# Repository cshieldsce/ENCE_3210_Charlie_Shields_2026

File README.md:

# ENCE 3210 - Microprocessor Systems I
All my labs, projects, and drivers for Microprocessor Systems I, Winter 2026.

---

## Project Documentation

### Documentation B - DAC Prototype & KiCad
> 📁 [`Documentation_B/`](Documentation_B/README.md)

- 5-bit R-2R DAQ prototype built in lab and verified on oscilloscope
- Falstad circuit simulation
- KiCad schematic and PCB layout files for the Arduino UNO Shield

### Documentation C - DSP Shield
> 📁 [`Documentation_C/`](Documentation_C/README.md)

Full documentation for the DSP Shield design and fabrication.

- Shield specifications and block diagram
- 10-bit R-2R Ladder DAC design and prototype
- KiCad PCB schematic, layout, 3D renders, and gerber files
- Interactive BOM
- Live demo videos of firmware running on the shield

---

## Labs

### Lab 1 — More C Practice
> 📁 [`lab1_embedded_c/`](labs/lab1_embedded_c/README.md)

Exercises practicing fundamental C programming concepts on embedded targets.

- Calculate twice the square of integers 0–511
- Cosine calculation for degrees 0–360 (results stored in array)
- Find the second maximum value in a 50-element integer array

---

### Lab 2 — Interrupts
> 📁 [`lab2_interrupts/`](labs/lab2_interrupts/README.md)

C programs using Interrupt Service Routines (ISRs) on the Arduino UNO.

- **Button Counter:** Count presses of two buttons via ISR; drive RGB LED based on difference
- **LED Sequence Control:** Cycle through R → RG → RGB → GB → B → RB on button press
- **Simple Calculator:** ISR-driven arithmetic operations
- **Filtering Operation:** Basic signal filtering using interrupts

---

### Lab 3 — Asynchronous Tasks with Interrupt Timers
> 📁 [`lab3_async_tasks/`](labs/lab3_async_tasks/README.md)

Two background tasks and one foreground task running concurrently using hardware timers.

| Task | Frequency | Timer | Responsibility |
|---|---|---|---|
| Task 1 | 1 Hz | Timer 1 | Blink Green LED, increment main-task counter |
| Task 2 | 10 Hz | Timer 2 | Additional async operation |
| Main | — | — | Foreground logic driven by Task 1 counter |

Also includes a **5-bit R-2R DAQ circuit** built and tested with oscilloscope verification.

---

### Lab 4 — Firmware Engineering
> 📁 [`lab4_firmware/`](labs/lab4_firmware/README.md)

Firmware design exercises built and tested on the DSP Shield.

- **Exercise 2 — Solar Charger:** Firmware for a solar charging control system
- **Exercise 4 — Fan Controller:** PWM-based fan speed controller with block diagram

> Demo videos for both projects available in [`Documentation_C/`](Documentation_C/README.md#shield-demos)

---

## HAL Drivers
> 📁 [`HAL_Drivers/`](HAL_Drivers/README.md)

Reusable hardware abstraction layer drivers developed during the course.

| Driver | Description |
|---|---|
| `ADCs_Uno/` | ADC read utilities for Arduino UNO |
| `PWMs_Uno/` | PWM output utilities for Arduino UNO |
| `HC_SR04_Drivers_v1/` | HC-SR04 ultrasonic sensor driver (v1) |
| `HC_SR04_Drivers_v2/` | HC-SR04 driver with interrupt support (v2) |
| `HC_SR04_Drivers_v3/` | HC-SR04 driver with filtered output (v3) |
| `MPU6050_Test/` | MPU-6050 IMU (I2C) test and driver |
| `SSD1306_Test/` | SSD1306 OLED HAL driver test |

---

## C Workshop
> 📁 [`c_workshop/`](c_workshop/README.md)

Warm-up C programming exercises completed at the start of the course.

- `quadratic.c` — Solve quadratic equations using a struct to return both roots
- `scanf_for_loop.c` — User input processing with for loops

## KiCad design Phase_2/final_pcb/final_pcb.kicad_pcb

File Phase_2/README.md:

# Phase 2 - DemoSat PCB Design

**ENCE 3210 Microprocessors 1 | Winter Quarter 2026 | Final Project**
**Created by: Charlie Shields**

---

## Overview

This phase contains the final custom PCB design for the DemoSat project — a sensor data logging system built around an Arduino Uno (ATmega328P). The board interfaces with multiple sensors, logs data to a microSD card, and provides visual status indicators.

---

## System Block Diagram

---

## PCB Preview

### Front Silkscreen

### 3D Render

---

## System Architecture

The PCB acts as a shield/carrier board for the Arduino Uno and integrates the following components:

| Component | Function | Interface |
|---|---|---|
| SparkFun LIS3DH Breakout | 3-Axis Accelerometer | I2C (SDA/SCL) |
| Adafruit MS8607 | External Temp, Humidity, Pressure | I2C (SDA/SCL) |
| TMP36 | Internal Temperature Sensor | Analog (A0) |
| SparkFun OpenLog | Serial Data Logger → microSD | UART (TX/D1) |
| 4x LEDs (LED1–LED4) | Status Indicators | D5, D6, D7, D9 |
| LD1117V33 | 3.3V Voltage Regulator | Power |
| SW1 | Power Switch | — |
| 9V Battery Connector | Power Input | — |

---

## Repository Structure

```
Phase_2/
├── final_pcb/               # KiCad project files
│   ├── final_pcb.kicad_pcb  # PCB layout
│   ├── final_pcb.kicad_sch  # Schematic
│   ├── bom/
│   │   └── ibom.html        # Interactive BOM
│   ├── docs/
│   │   └── images/          # KiCad PCB Images
│   ├── gerber/              # Fabrication files
│   └── libraries/           # Custom footprints & symbols
│       ├── Adafruit MS8607/
│       ├── DEV-13712/
│       ├── SparkFun_LIS3DH-Breakout/
│       ├── TMP36GT9/
│       └── logos/           # COSGC, CU, DU logos
└── Final Presentation.pdf
```

---

## PCB Details

- **Layers:** 2 (F.Cu / B.Cu)
- **Connectors:** J1, J2, J3 (Arduino header passthrough)
- **Decoupling Caps:** C1, C2, C3
- **Current Limiting Resistors:** R1–R4 (for LEDs)
- **Mounting Holes:** 4x corners

---

## Tools Used

- [KiCad](https://www.kicad.org/) — Schematic & PCB design
- [draw.io](https://draw.io) — System block diagram

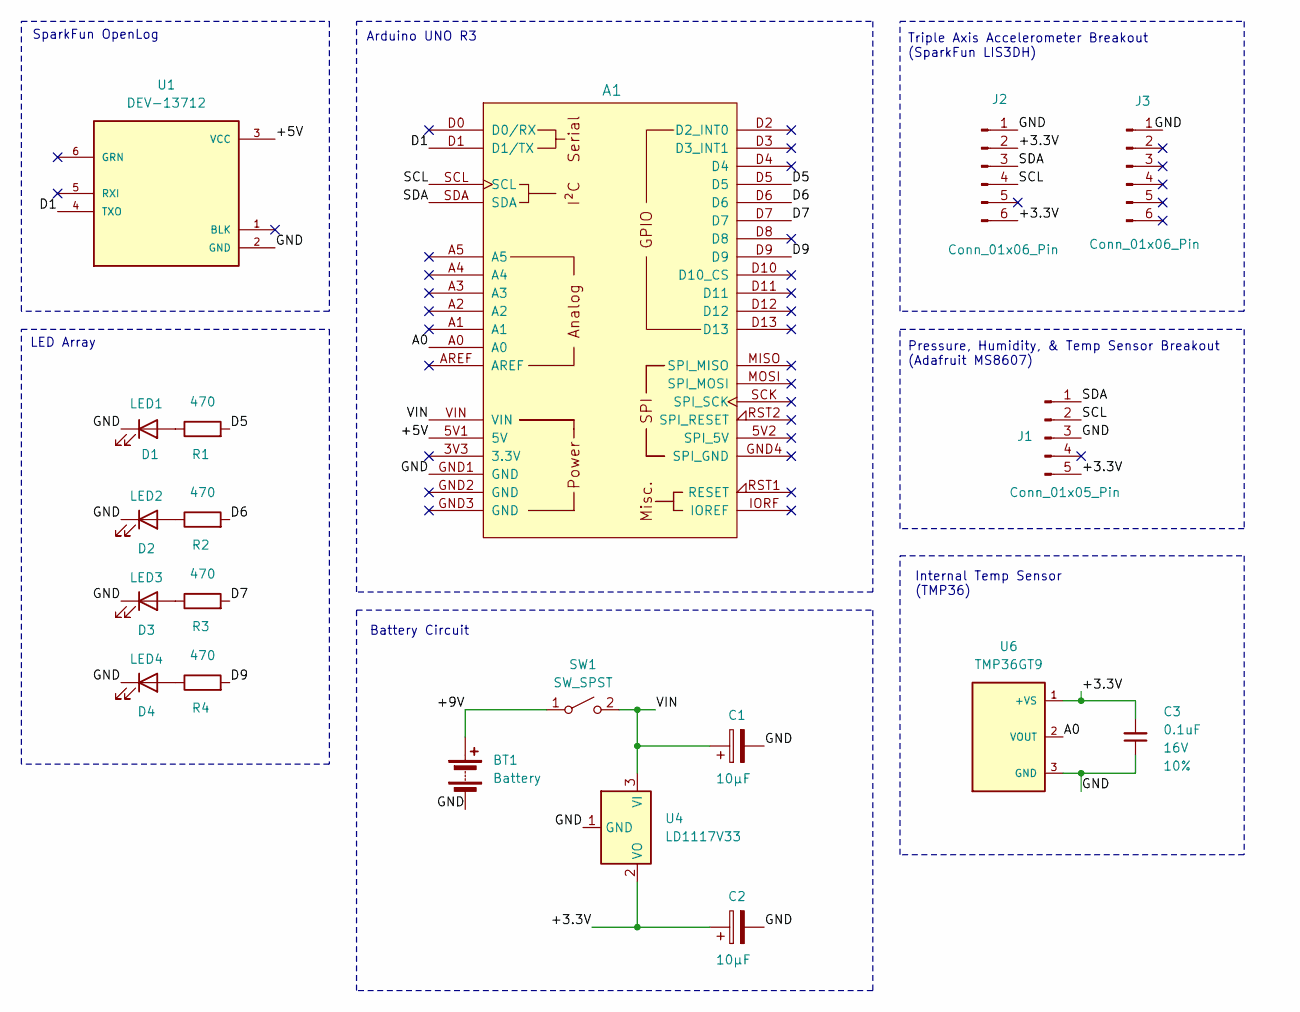
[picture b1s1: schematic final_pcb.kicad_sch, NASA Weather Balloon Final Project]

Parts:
A1: Arduino_Uno_R3_Shield
BT1: Battery; PinHeader_1x02_P2.54mm_Vertical
C1, C2: 10µF; CP_Radial_D5.0mm_P2.00mm
C3: 0.1uF; C_Disc_D3.0mm_W1.6mm_P2.50mm; Voltage 16V; Tolerance 10%
D1: LED1; LED_D3.0mm
D2: LED2; LED_D3.0mm
D3: LED3; LED_D3.0mm
D4: LED4; LED_D3.0mm
J1: Conn_01x05_Pin; PinHeader_1x05_P2.54mm_Vertical
J2, J3: Conn_01x06_Pin; PinHeader_1x06_P2.54mm_Vertical
R1, R2, R3, R4: 470; R_Axial_DIN0207_L6.3mm_D2.5mm_P7.62mm_Horizontal
SW1: SW_SPST; PinHeader_1x02_P2.54mm_Vertical
U1: DEV-13712; MODULE_DEV-13712; PARTREV v15
U4: LD1117V33; TO-220-3_Vertical
U6: TMP36GT9; XDCR_TMP36GT9; PARTREV H

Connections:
/+3.3V: C2.1, C3.2, J1.5, J2.2, J2.6, U4.2 (VO), U6.1 (+VS)
/+5V: A1.5V1 (5V), U1.3 (VCC)
/+9V: BT1.1 (+), SW1.1 (A)
/A0: A1.A0, U6.2 (VOUT)
/D1: A1.D1 (D1/TX), U1.4 (TXO)
/D5: A1.D5, R1.2
/D6: A1.D6, R2.2
/D7: A1.D7, R3.2
/D9: A1.D9, R4.2
/GND: A1.GND1 (GND), BT1.2 (-), C1.2, C2.2, C3.1, D1.1 (K), D2.1 (K), D3.1 (K), D4.1 (K), J1.3, J2.1, J3.1, U1.2 (GND), U4.1 (GND), U6.3 (GND)
/SCL: A1.SCL, J1.2, J2.4
/SDA: A1.SDA, J1.1, J2.3
/VIN: A1.VIN, C1.1, SW1.2 (B), U4.3 (VI)
unnamed: D1.2 (A), R1.1
unnamed: D2.2 (A), R2.1
unnamed: D3.2 (A), R3.1
unnamed: D4.2 (A), R4.1

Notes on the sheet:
Pressure, Humidity, & Temp Sensor Breakout (Adafruit MS8607)
Arduino UNO R3
SparkFun OpenLog
LED Array
Triple Axis Accelerometer Breakout (SparkFun LIS3DH)
Internal Temp Sensor (TMP36)
Battery Circuit

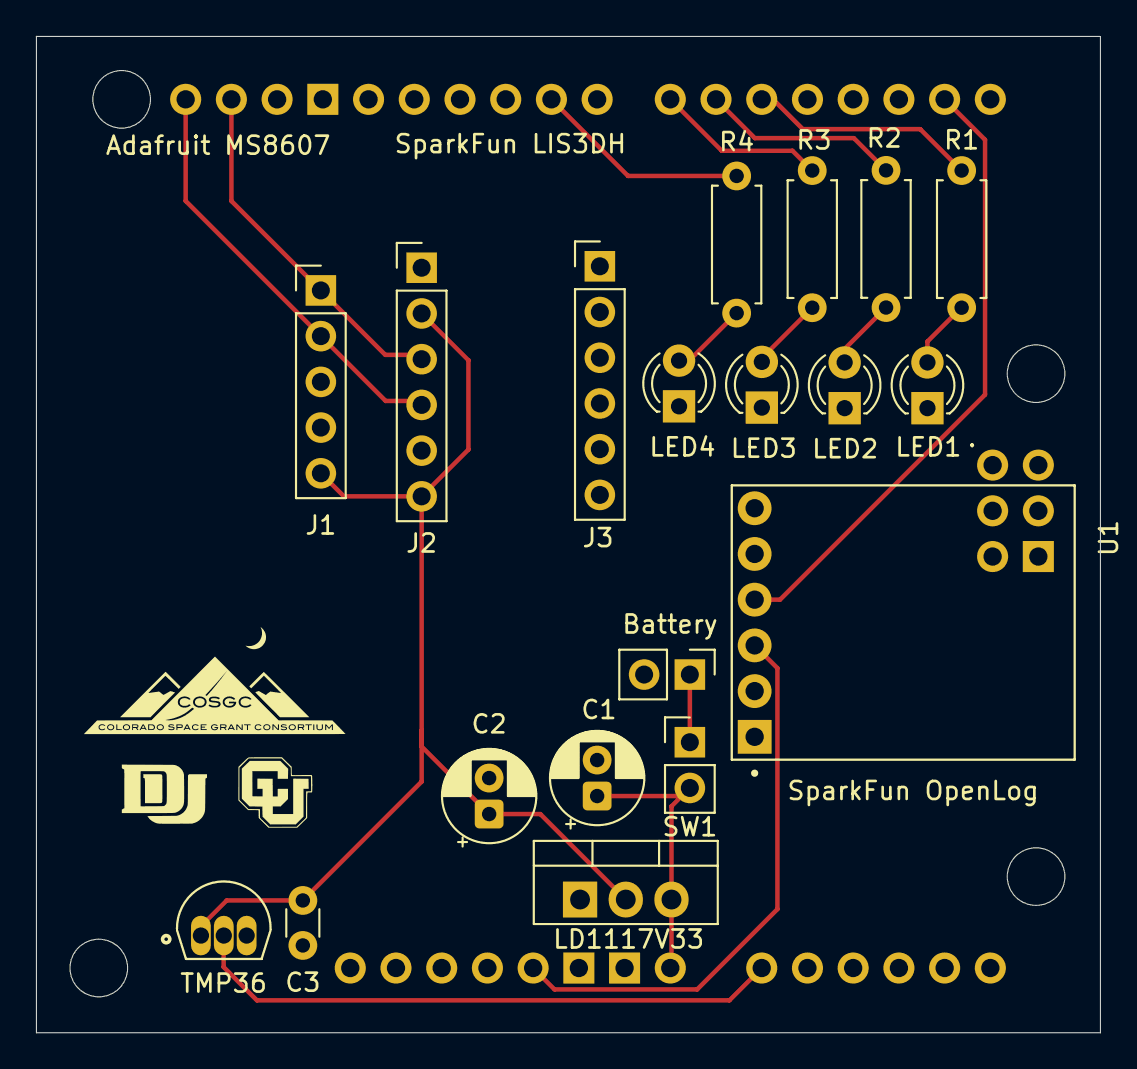
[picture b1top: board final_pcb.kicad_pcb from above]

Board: 2 copper layers, 59.1 x 55.3 mm, 20 parts (0 on the bottom side), 17 nets.

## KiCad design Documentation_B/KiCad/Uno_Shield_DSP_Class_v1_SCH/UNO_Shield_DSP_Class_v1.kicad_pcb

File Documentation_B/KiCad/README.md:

# Arduino UNO Shield PCB V1
See `Uno_Shield_DSP_Class_v1_SCH/` for the KiCad project files.

## Project Images

**3D View**:

**PCB Schematic**:

**PCB Board Front View**:

**PCB Board Back View**:

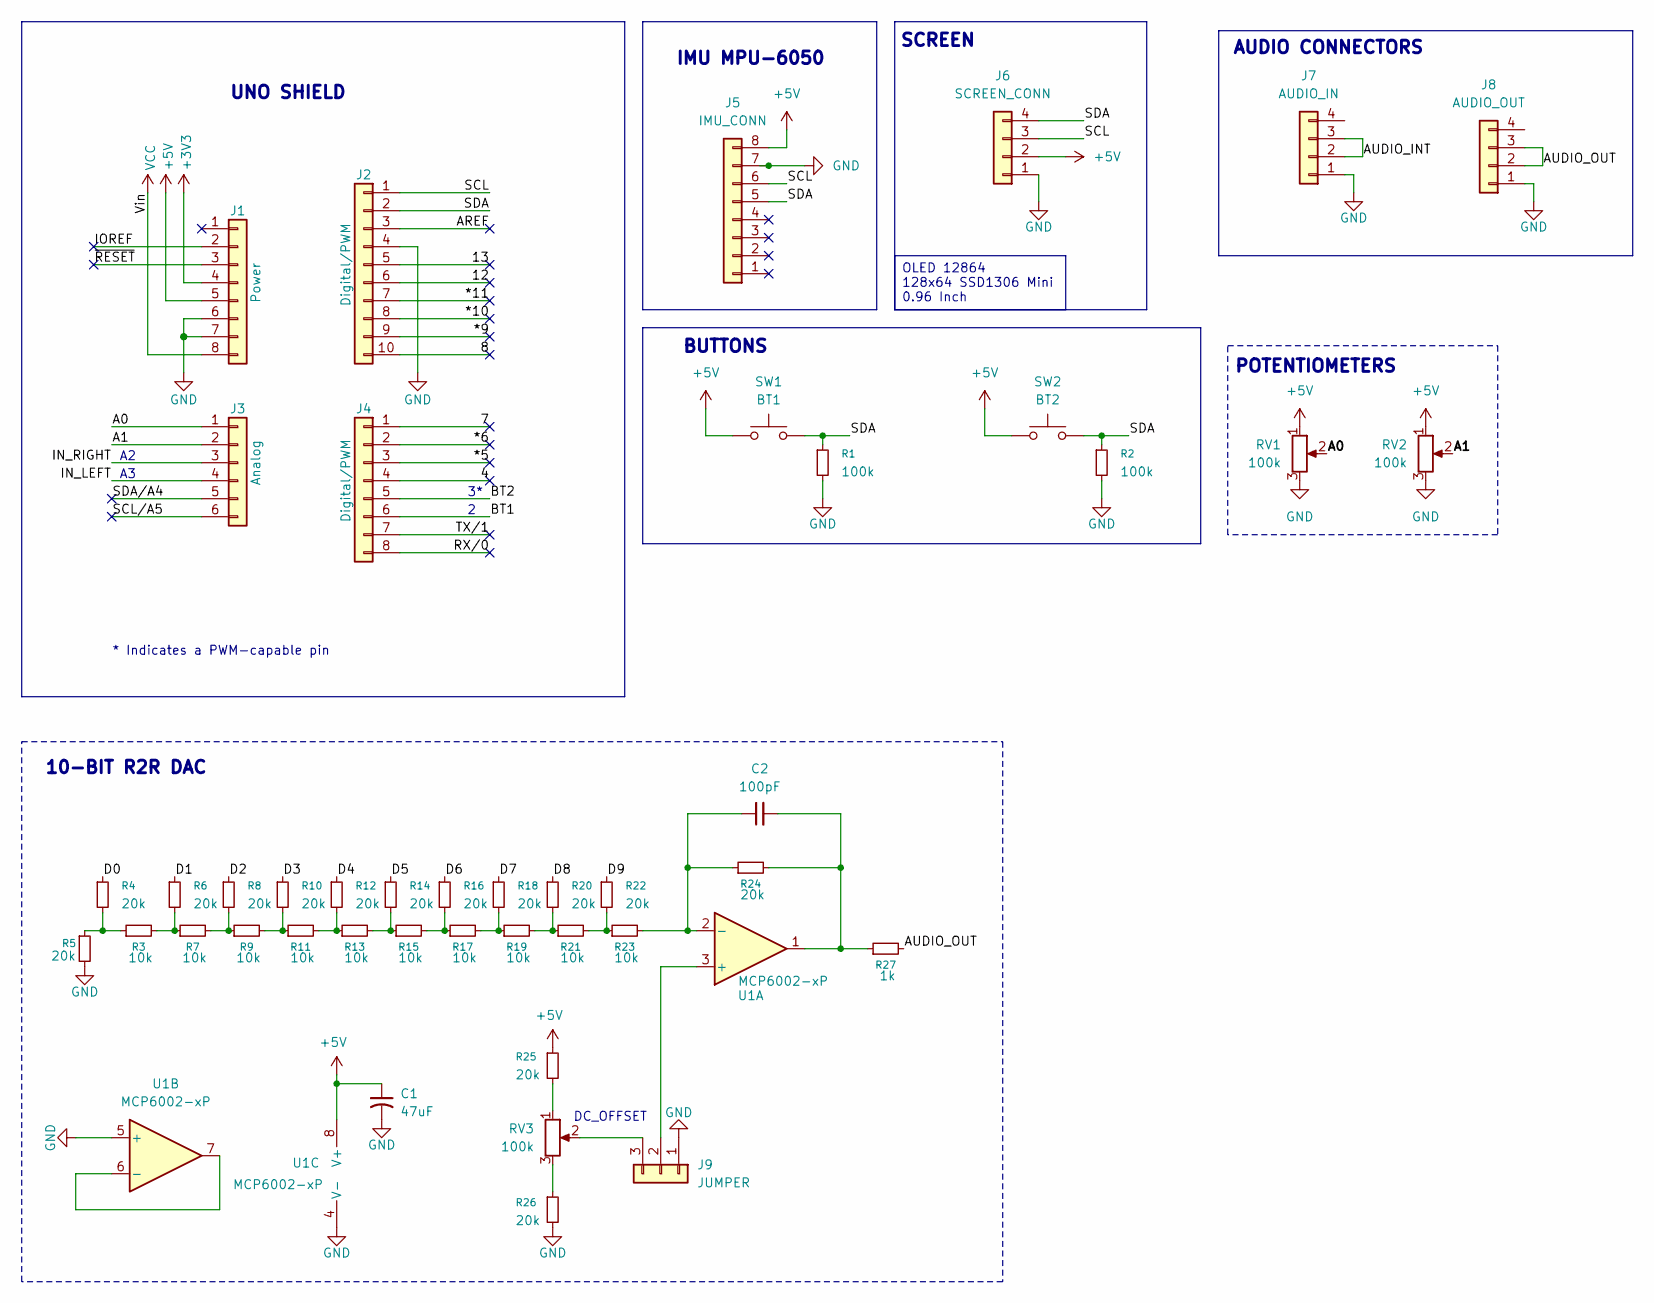
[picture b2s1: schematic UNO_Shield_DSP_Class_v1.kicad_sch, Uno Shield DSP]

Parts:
C1: 47uF; C_Radial_D6.3mm_H11.0mm_P2.50mm
C2: 100pF; C_Disc_D5.0mm_W2.5mm_P2.50mm
J1: Power; PinSocket_1x08_P2.54mm_Vertical
J2: Digital/PWM; PinSocket_1x10_P2.54mm_Vertical
J3: Analog; PinSocket_1x06_P2.54mm_Vertical
J4: Digital/PWM; PinSocket_1x08_P2.54mm_Vertical
J5: IMU_CONN; PinSocket_1x08_P2.54mm_Vertical
J6: SCREEN_CONN; PinHeader_1x04_P2.54mm_Vertical
J7: AUDIO_IN; PinHeader_1x04_P2.54mm_Vertical
J8: AUDIO_OUT; PinHeader_1x04_P2.54mm_Vertical
J9: JUMPER; PinHeader_1x03_P2.54mm_Vertical
R1, R2: 100k; R_Axial_DIN0309_L9.0mm_D3.2mm_P2.54mm_Vertical
R3, R7, R9, R11, R13, R15, R17, R19, R21, R23: 10k; R_Axial_DIN0309_L9.0mm_D3.2mm_P2.54mm_Vertical
R4, R5, R6, R8, R10, R12, R14, R16, R18, R20, R22, R24, R25, R26: 20k; R_Axial_DIN0309_L9.0mm_D3.2mm_P2.54mm_Vertical
R27: 1k; R_Axial_DIN0309_L9.0mm_D3.2mm_P2.54mm_Vertical
RV1, RV2, RV3: 100k; Potentiometer_Bourns_3386P_Vertical
SW1: BT1; SW_PUSH_6mm
SW2: BT2; SW_PUSH_6mm
U1: MCP6002-xP; DIP-8_W7.62mm_Socket_LongPads

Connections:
+3V3: J1.4
+5V: C1.1, J1.5, J5.8, J6.2, R25.1, RV1.1, RV2.1, SW1.1, SW2.1, U1.8 (V+)
/4: J4.4
/7: J4.1
/8: J2.10
/12: J2.6
/13: J2.5
/*5: J4.3
/*6: J4.2
/*9: J2.9
/*10: J2.8
/*11: J2.7
/A0: J3.1, RV1.2
/A1: J3.2, RV2.2
/AREF: J2.3
/AUDIO_INT: J7.2, J7.3
/AUDIO_OUT: J8.2, J8.3, R27.2
/BT1: J4.6
/BT2: J4.5
/D0: R4.1
/D1: R6.1
/D2: R8.1
/D3: R10.1
/D4: R12.1
/D5: R14.1
/D6: R16.1
/D7: R18.1
/D8: R20.1
/D9: R22.1
/IN_LEFT: J3.4
/IN_RIGHT: J3.3
/IOREF: J1.2
/RX/0: J4.8
/SCL: J2.1, J5.6, J6.3
/SCL/A5: J3.6
/SDA: J2.2, J5.5, J6.4, R1.1, R2.1, SW1.2, SW2.2
/SDA/A4: J3.5
/TX/1: J4.7
/~RESET: J1.3
GND: C1.2, J1.6, J1.7, J2.4, J5.7, J6.1, J7.1, J8.1, J9.1, R1.2, R2.2, R5.2, R26.2, RV1.3, RV2.3, U1.4 (V-), U1.5 (+)
unnamed: C2.2, R24.2, R27.1, U1.1
unnamed: J9.2, U1.3 (+)
unnamed: J9.3, RV3.2
unnamed: R3.1, R4.2, R5.1
unnamed: R3.2, R6.2, R7.1
unnamed: R7.2, R8.2, R9.1
unnamed: R9.2, R10.2, R11.1
unnamed: R11.2, R12.2, R13.1
unnamed: R13.2, R14.2, R15.1
unnamed: R15.2, R16.2, R17.1
unnamed: R17.2, R18.2, R19.1
unnamed: R19.2, R20.2, R21.1
unnamed: R21.2, R22.2, R23.1
unnamed: R25.2, RV3.1
unnamed: R26.1, RV3.3
unnamed: C2.1, R23.2, R24.1, U1.2 (-)
unnamed: U1.6 (-), U1.7
VCC: J1.8

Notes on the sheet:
10-BIT R2R DAC
IMU MPU-6050
SCREEN
AUDIO CONNECTORS
BUTTONS
* Indicates a PWM-capable pin
DC_OFFSET
POTENTIOMETERS
UNO SHIELD
OLED 12864 128x64 SSD1306 Mini 0.96 Inch

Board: 2 copper layers, 48 parts (0 on the bottom side), 25 nets, no tracks yet.

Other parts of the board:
MH1, MH2, MH3, MH4: MountingHole_3.2mm

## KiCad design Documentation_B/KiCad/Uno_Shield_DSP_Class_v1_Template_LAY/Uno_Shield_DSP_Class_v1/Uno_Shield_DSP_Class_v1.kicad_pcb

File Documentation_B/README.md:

# Documentation B — DAC Prototype & KiCad Schematics

Supporting documentation for the Arduino UNO Shield project.

---

## DAC Prototype
> 📁 [`DAC_Prototype/`](DAC_Prototype/README.md)

A 5-bit R-2R resistor ladder DAC prototype built and tested in lab.

- Arduino sets the DAC's 5 input bits to generate output voltage steps
- Output staircase waveform verified on oscilloscope
- Falstad simulation included: `circuit_5bit_r2r_daq`

---

## KiCad Schematics
> 📁 [`KiCad/`](KiCad/)

KiCad schematic and PCB layout files for the Arduino UNO Shield.

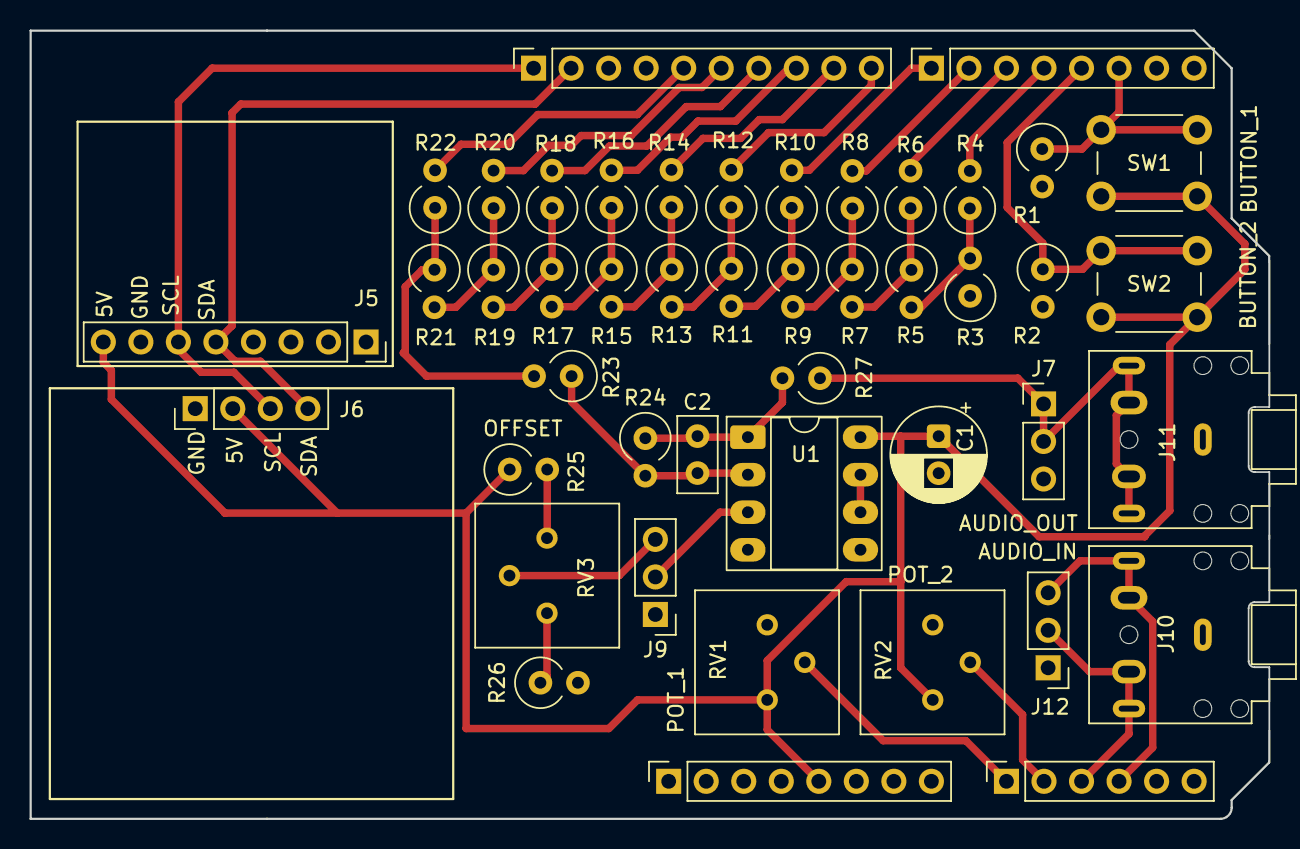
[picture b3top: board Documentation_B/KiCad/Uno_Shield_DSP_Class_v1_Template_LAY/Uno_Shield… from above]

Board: 2 copper layers, 83.8 x 53.3 mm, 46 parts (0 on the bottom side), 38 nets.

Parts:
C1: 47uF; CP_Radial_D6.3mm_P2.50mm
C2: 100pF; C_Disc_D5.0mm_W2.5mm_P2.50mm
J1: Power; PinSocket_1x08_P2.54mm_Vertical
J2: Digital/PWM; PinSocket_1x10_P2.54mm_Vertical
J3: Analog; PinSocket_1x06_P2.54mm_Vertical
J4: Digital/PWM; PinSocket_1x08_P2.54mm_Vertical
J5: IMU_CONN; PinSocket_1x08_P2.54mm_Vertical
J6: SCREEN_CONN; PinHeader_1x04_P2.54mm_Vertical
J7: AUDIO_OUT; PinHeader_1x03_P2.54mm_Vertical
J9: JUMPER; PinHeader_1x03_P2.54mm_Vertical
J10, J11: AudioJack5; Jack_3.5mm_CUI_SJ1-3525N_Horizontal
J12: AUDIO_IN; PinHeader_1x03_P2.54mm_Vertical
R1, R2: 100k; R_Axial_DIN0309_L9.0mm_D3.2mm_P2.54mm_Vertical
R3, R4, R6, R8, R10, R12, R14, R16, R18, R20, R22, R23, R24, R25, R26: 20k; R_Axial_DIN0309_L9.0mm_D3.2mm_P2.54mm_Vertical
R5, R7, R9, R11, R13, R15, R17, R19, R21: 10k; R_Axial_DIN0309_L9.0mm_D3.2mm_P2.54mm_Vertical
R27: 1k; R_Axial_DIN0309_L9.0mm_D3.2mm_P2.54mm_Vertical
RV1, RV2, RV3: 100k; Potentiometer_Bourns_3386P_Vertical
SW1: BT_1; SW_PUSH_6mm
SW2: BT_2; SW_PUSH_6mm
U1: MCP6002-xP; DIP-8_W7.62mm_Socket_LongPads

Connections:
+5V: C1.1, J1.5, J5.8, J6.2, R25.1, RV1.1, RV2.1, SW1.1, SW2.1, U1.8 (V+)
/A0: J3.1, RV1.2
/A1: J3.2, RV2.2
/AUDIO_OUT: J7.1, J7.2, J11.R, J11.RN, J11.T, J11.TN, R27.1
/BT1: J4.6, R1.1, SW1.2
/BT2: J4.5, R2.1, SW2.2
/D0: J4.4, R4.2
/D1: J4.3, R6.2
/D2: J4.2, R8.2
/D3: J4.1, R10.2
/D4: J2.10, R12.2
/D5: J2.9, R14.2
/D6: J2.8, R16.2
/D7: J2.7, R18.2
/D8: J2.6, R20.2
/D9: J2.5, R22.2
/IN_LEFT: J3.4, J10.T, J10.TN, J12.3
/IN_RIGHT: J3.3, J10.R, J10.RN, J12.2
/SCL: J2.1, J5.6, J6.3
/SDA: J2.2, J5.5, J6.4
GND: C1.2, J1.6, J1.7, J2.4, J5.7, J6.1, J7.3, J9.1, J10.S, J11.S, J12.1, R1.2, R2.2, R3.1, R26.2, RV1.3, RV2.3, U1.4 (V-), U1.5 (+)
unnamed: C2.2, R24.1, R27.2, U1.1
unnamed: J9.2, U1.3 (+)
unnamed: J9.3, RV3.2
unnamed: R3.2, R4.1, R5.2
unnamed: R5.1, R6.1, R7.2
unnamed: R7.1, R8.1, R9.2
unnamed: R9.1, R10.1, R11.2
unnamed: R11.1, R12.1, R13.2
unnamed: R13.1, R14.1, R15.2
unnamed: R15.1, R16.1, R17.2
unnamed: R17.1, R18.1, R19.2
unnamed: R19.1, R20.1, R21.2
unnamed: R21.1, R22.1, R23.2
unnamed: R25.2, RV3.1
unnamed: R26.1, RV3.3
unnamed: C2.1, R23.1, R24.2, U1.2 (-)
unnamed: U1.6 (-), U1.7

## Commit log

2026-01-12 Add comments to workshop problems and add lab1 folder structure
2026-01-12 update readmes
2026-01-16 Finish Lab1
2026-01-16 Add video demos to README for questions 6 and 7
    Added video demos for LED sequence control and simple calculator.
2026-01-16 Update Lab1
2026-01-16 Lab2
2026-01-22 Finish Lab2
2026-03-09 Documentation C
2026-03-09 update Documentation C
2026-03-09 add Phase 1
2026-03-09 update README.md filename
2026-03-09 fix spacing
2026-03-09 fix typo
2026-03-13 Add Phase 2
2026-03-13 Add Phase 2 README.md
2026-06-28 Clean up README formatting and course info
    Removed unnecessary formatting characters and updated course info section.
2026-06-28 Enhance README with project documentation sections
    Added detailed project documentation for DAC Prototype and DSP Shield, including specifications, designs, and demo videos.
